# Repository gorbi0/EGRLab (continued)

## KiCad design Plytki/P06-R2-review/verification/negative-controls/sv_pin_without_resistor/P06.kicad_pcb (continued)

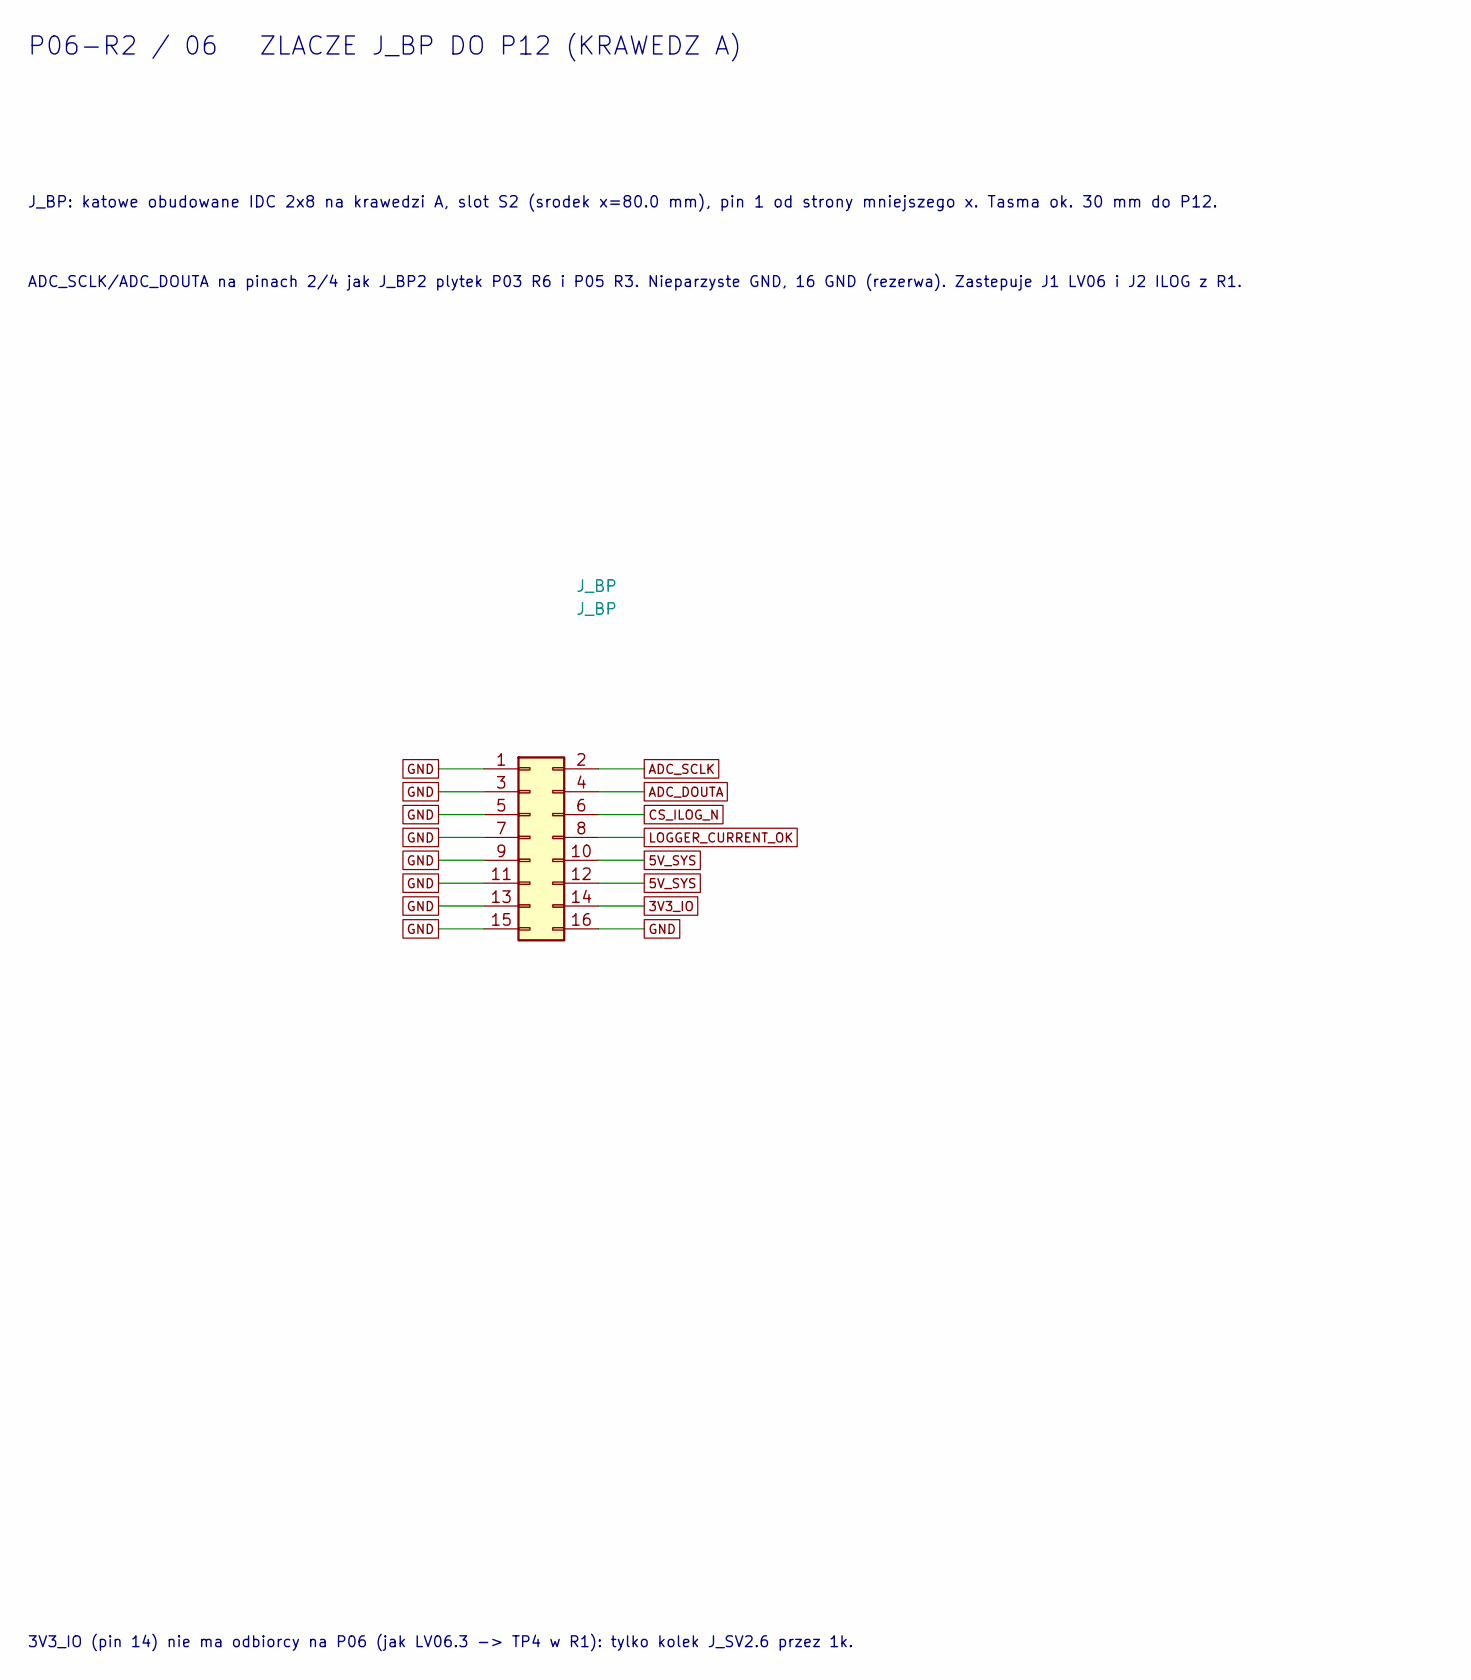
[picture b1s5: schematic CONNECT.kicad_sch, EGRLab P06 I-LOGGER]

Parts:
J_BP: J_BP; IDC-Header_2x08_P2.54mm_Horizontal; MPN IDC header 2x8 2.54mm angled shrouded, 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

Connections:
3V3_IO: J_BP.14; also elsewhere on the board
ADC_DOUTA: J_BP.4; also elsewhere on the board
ADC_SCLK: J_BP.2; also elsewhere on the board
CS_ILOG_N: J_BP.6; also elsewhere on the board
GND: J_BP.1, J_BP.3, J_BP.5, J_BP.7, J_BP.9, J_BP.11, J_BP.13, J_BP.15, J_BP.16; also elsewhere on the board
LOGGER_CURRENT_OK: J_BP.8; also elsewhere on the board

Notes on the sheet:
J_BP: katowe obudowane IDC 2x8 na krawedzi A, slot S2 (srodek x=80.0 mm), pin 1 od strony mniejszego x. Tasma ok. 30 mm do P12.
ADC_SCLK/ADC_DOUTA na pinach 2/4 jak J_BP2 plytek P03 R6 i P05 R3. Nieparzyste GND, 16 GND (rezerwa). Zastepuje J1 LV06 i J2 ILOG z R1.
3V3_IO (pin 14) nie ma odbiorcy na P06 (jak LV06.3 -> TP4 w R1): tylko kolek J_SV2.6 przez 1k.
P06-R2 / 06 ZLACZE J_BP DO P12 (KRAWEDZ A)

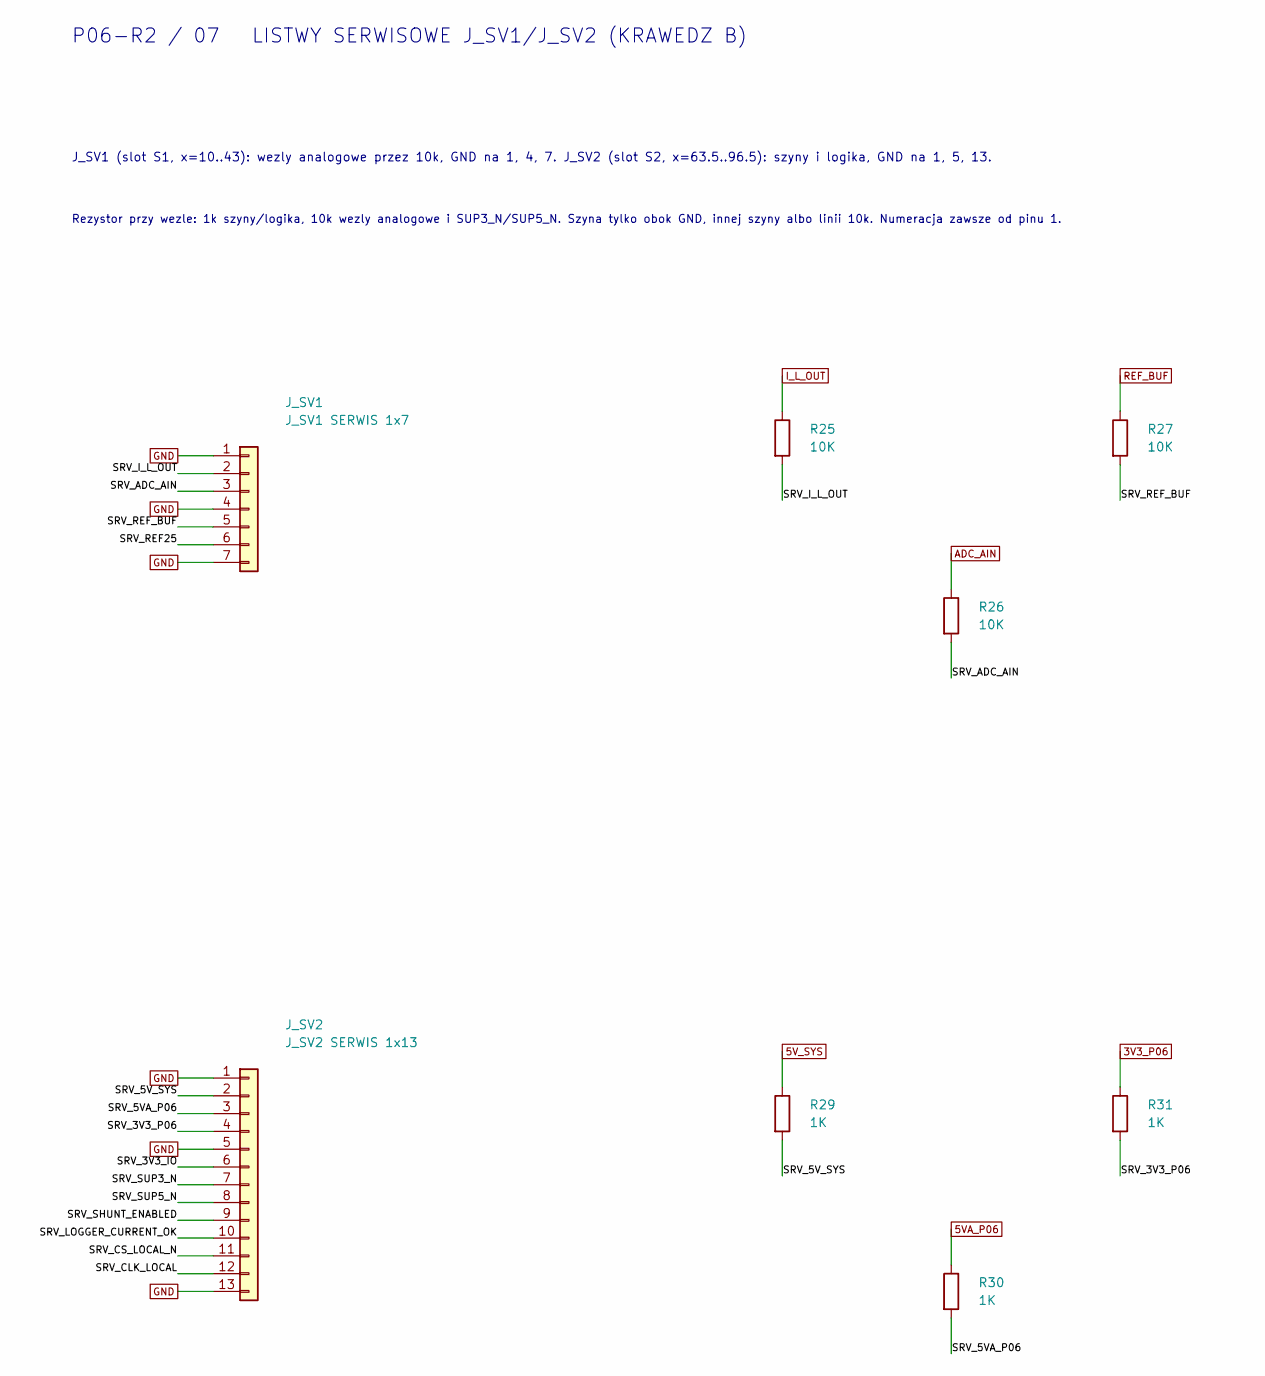
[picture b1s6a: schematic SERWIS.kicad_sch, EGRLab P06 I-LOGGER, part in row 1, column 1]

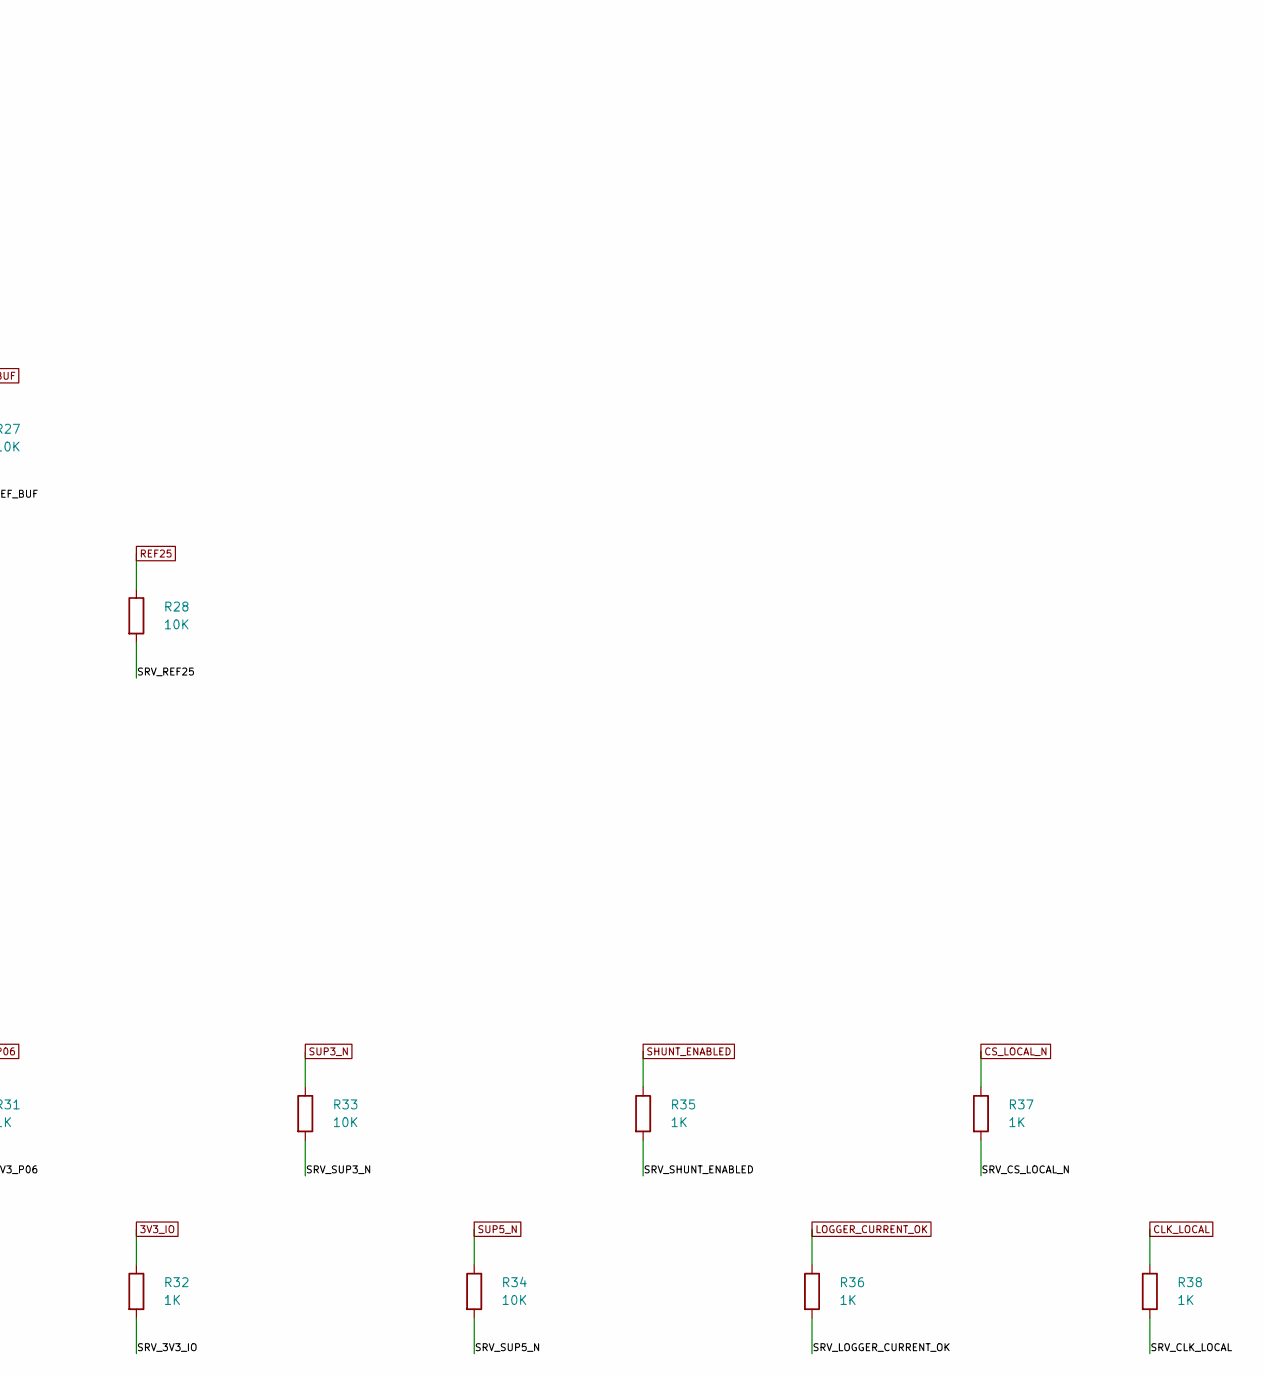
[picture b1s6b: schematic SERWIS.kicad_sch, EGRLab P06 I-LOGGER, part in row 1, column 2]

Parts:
J_SV1: J_SV1 SERWIS 1x7; PinHeader_1x07_P2.54mm_Horizontal; MPN Pin header 1x7, 2.54 mm, right angle, Au
J_SV2: J_SV2 SERWIS 1x13; PinHeader_1x13_P2.54mm_Horizontal; MPN Pin header 1x13, 2.54 mm, right angle, 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
R25, R26, R27, R28, R33, R34: 10K; R_1206_3216Metric_Pad1.30x1.75mm_HandSolder; MPN RC1206FR-0710KL
R29, R30, R31, R32, R35, R36, R37, R38: 1K; R_1206_3216Metric_Pad1.30x1.75mm_HandSolder; MPN RC1206FR-071KL

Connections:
3V3_IO: R32.1; also elsewhere on the board
3V3_P06: R31.1; also elsewhere on the board
5VA_P06: R30.1; also elsewhere on the board
/SERWIS/SRV_3V3_IO: J_SV2.6, R32.2
/SERWIS/SRV_3V3_P06: J_SV2.4, R31.2
/SERWIS/SRV_5VA_P06: J_SV2.3, R30.2
/SERWIS/SRV_ADC_AIN: J_SV1.3, R26.2
/SERWIS/SRV_CLK_LOCAL: J_SV2.12, R38.2
/SERWIS/SRV_CS_LOCAL_N: J_SV2.11, R37.2
/SERWIS/SRV_I_L_OUT: J_SV1.2, R25.2
/SERWIS/SRV_LOGGER_CURRENT_OK: J_SV2.10, R36.2
/SERWIS/SRV_REF25: J_SV1.6, R28.2
/SERWIS/SRV_REF_BUF: J_SV1.5, R27.2
/SERWIS/SRV_SHUNT_ENABLED: J_SV2.9, R35.2
/SERWIS/SRV_SUP3_N: J_SV2.7, R33.2
/SERWIS/SRV_SUP5_N: J_SV2.8, R34.2
ADC_AIN: R26.1; also elsewhere on the board
CLK_LOCAL: R38.1; also elsewhere on the board
CS_LOCAL_N: R37.1; also elsewhere on the board
GND: J_SV1.1, J_SV1.4, J_SV1.7, J_SV2.1, J_SV2.5, J_SV2.13; also elsewhere on the board
I_L_OUT: R25.1; also elsewhere on the board
LOGGER_CURRENT_OK: R36.1; also elsewhere on the board
REF25: R28.1; also elsewhere on the board
REF_BUF: R27.1; also elsewhere on the board
SHUNT_ENABLED: R35.1; also elsewhere on the board
SUP3_N: R33.1; also elsewhere on the board
SUP5_N: R34.1; also elsewhere on the board

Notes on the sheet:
J_SV1 (slot S1, x=10..43): wezly analogowe przez 10k, GND na 1, 4, 7. J_SV2 (slot S2, x=63.5..96.5): szyny i logika, GND na 1, 5, 13.
Rezystor przy wezle: 1k szyny/logika, 10k wezly analogowe i SUP3_N/SUP5_N. Szyna tylko obok GND, innej szyny albo linii 10k. Numeracja zawsze od pinu 1.
P06-R2 / 07 LISTWY SERWISOWE J_SV1/J_SV2 (KRAWEDZ B)

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
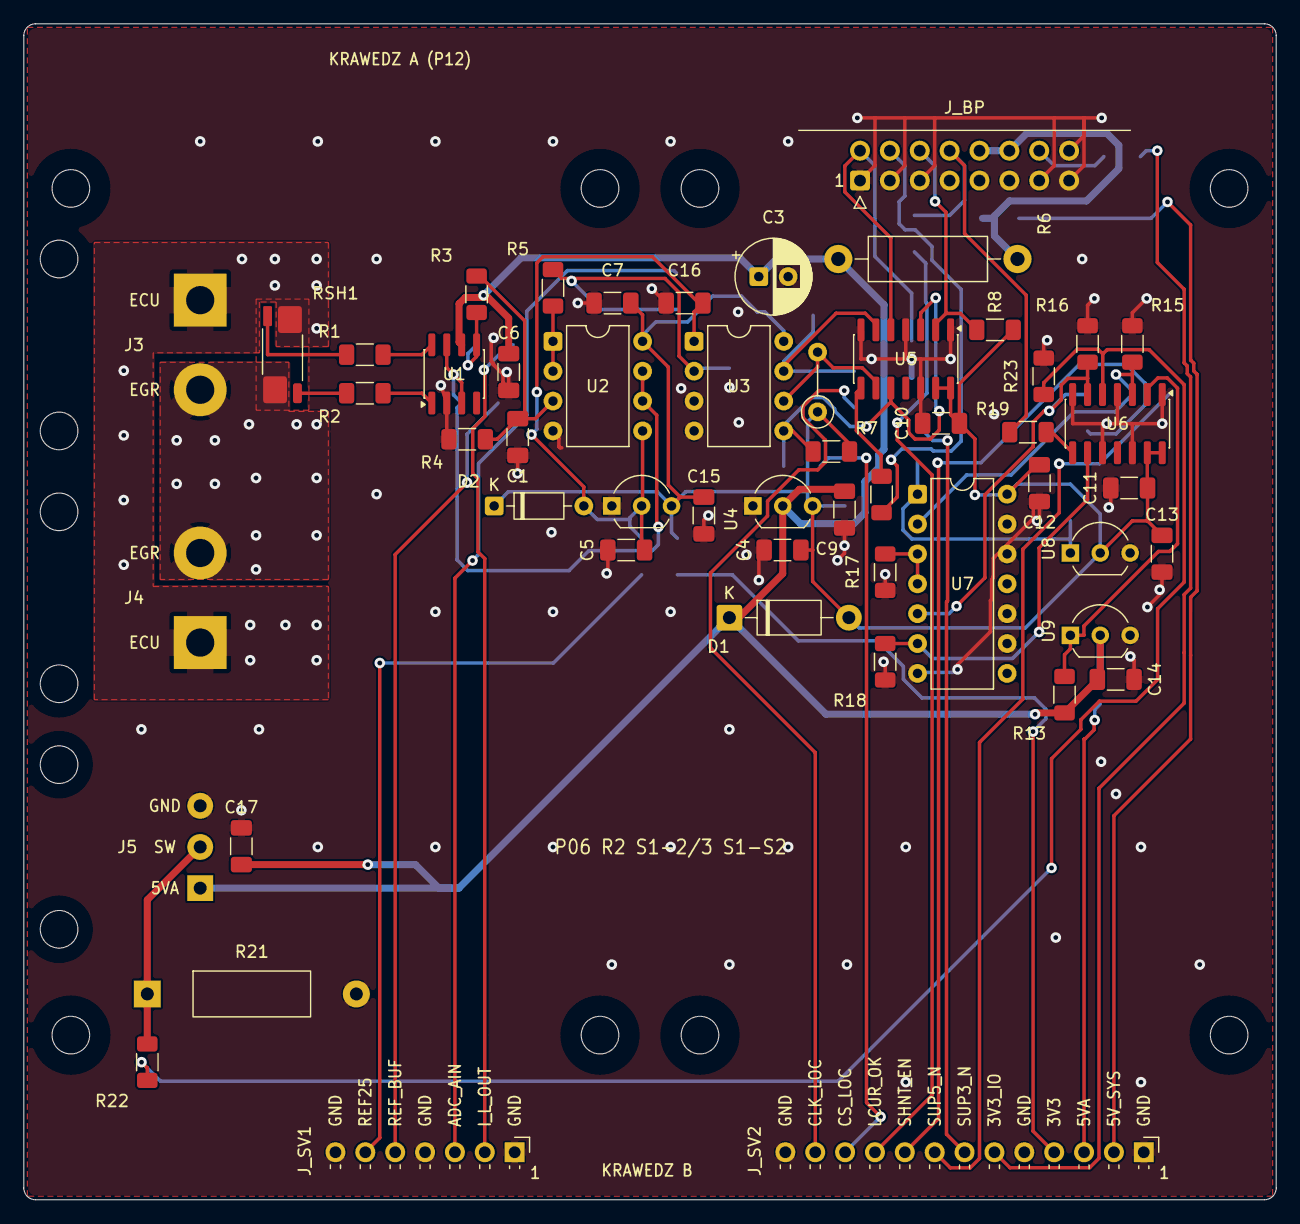
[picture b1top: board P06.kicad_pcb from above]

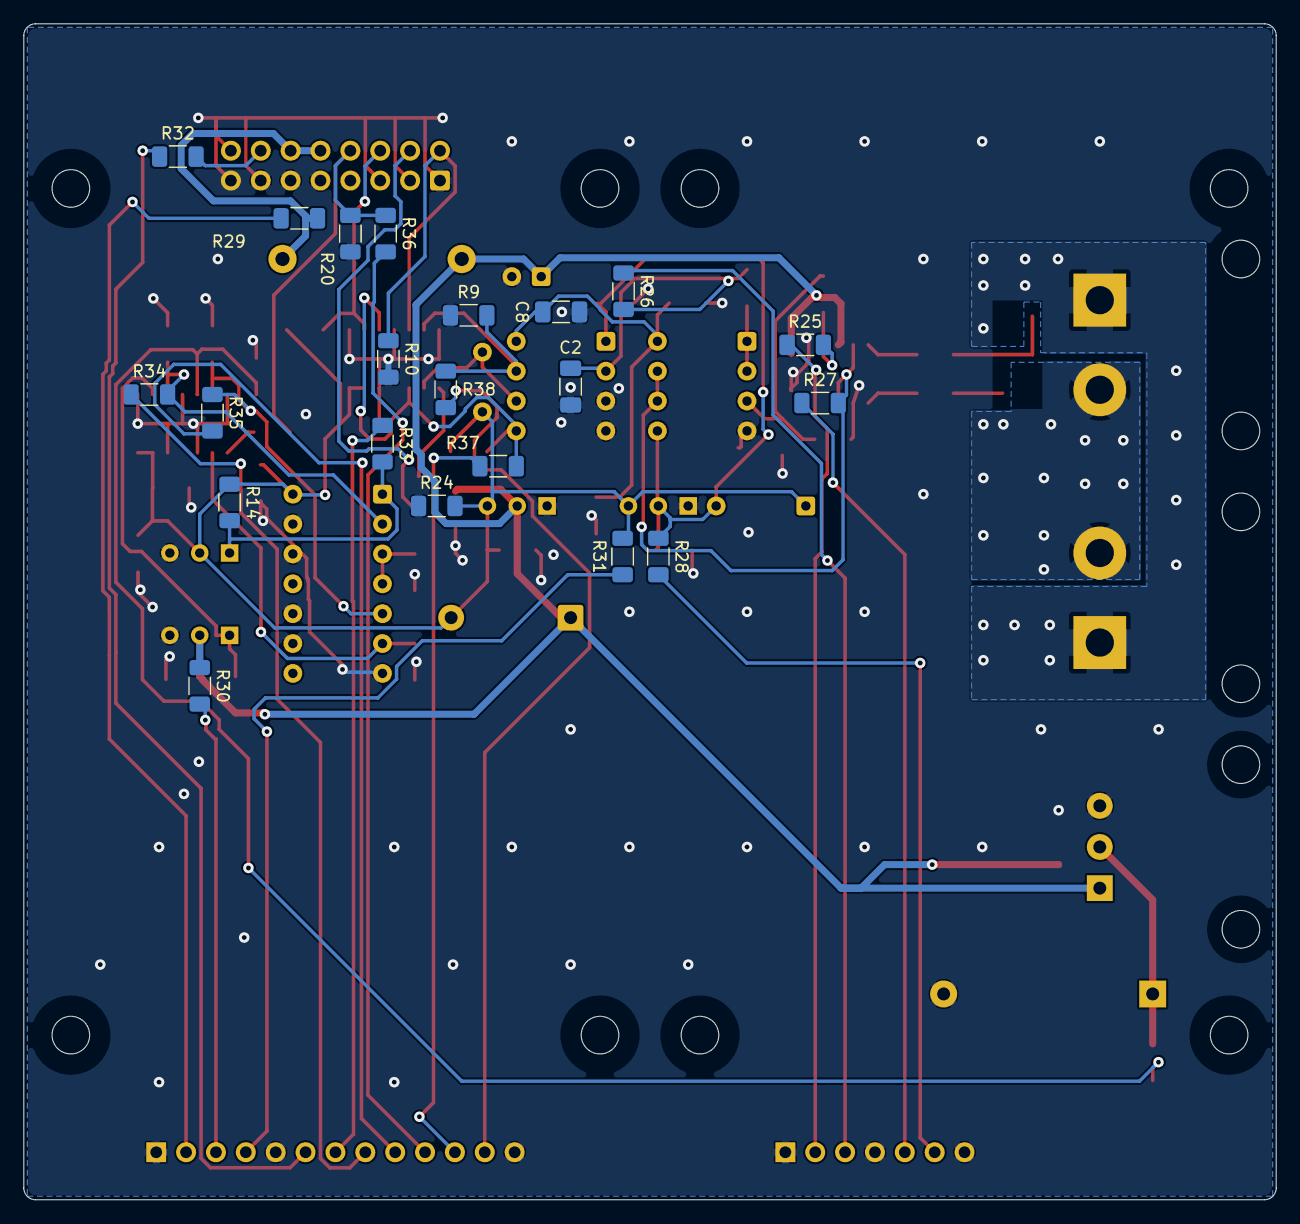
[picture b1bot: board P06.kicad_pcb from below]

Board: 2 copper layers, 106.5 x 100.0 mm, 82 parts (21 on the bottom side), 47 nets.

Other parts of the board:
C1: 470n; C_1206_3216Metric_Pad1.33x1.80mm_HandSolder
C5: 4.7u; C_1206_3216Metric_Pad1.33x1.80mm_HandSolder
C6: 100n; C_1206_3216Metric_Pad1.33x1.80mm_HandSolder
D2: BAT85; D_DO-35_SOD27_P7.62mm_Horizontal
H1, H2, H3, H4, H5, H6, H7, H8: M3 NPTH
R1, R2: 10R; R_1206_3216Metric_Pad1.30x1.75mm_HandSolder
R3, R4: 5.11K; R_1206_3216Metric_Pad1.30x1.75mm_HandSolder
U1: INA240A2; SOIC-8_3.9x4.9mm_P1.27mm
U10: MCP1525-I/TO; TO-92_Inline_Wide

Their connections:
3V3_P06: D2.1, U10.3; also elsewhere on the board
5VA_P06: C6.1, U1.6; also elsewhere on the board
/ANA/INA_MINUS: R2.2, U1.1
/ANA/INA_PLUS: R1.2, U1.8
/ANA/I_DIV: C1.1, R3.2, R4.1; also elsewhere on the board
GND: C1.2, C5.2, C6.2, R4.2, U1.2, U10.1; also elsewhere on the board
I_L_OUT: R3.1, U1.5; also elsewhere on the board
K_MINUS: R2.1; also elsewhere on the board
K_PLUS: R1.1; also elsewhere on the board
REF25: C5.1, D2.2, U10.2; also elsewhere on the board
REF_BUF: U1.3, U1.7; also elsewhere on the board
